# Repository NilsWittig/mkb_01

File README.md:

# mkb_01
Mechanical Keyboard 75%

https://www.instructables.com/STM32-As-HID-USB-Keyboard-STM32-Tutorials/

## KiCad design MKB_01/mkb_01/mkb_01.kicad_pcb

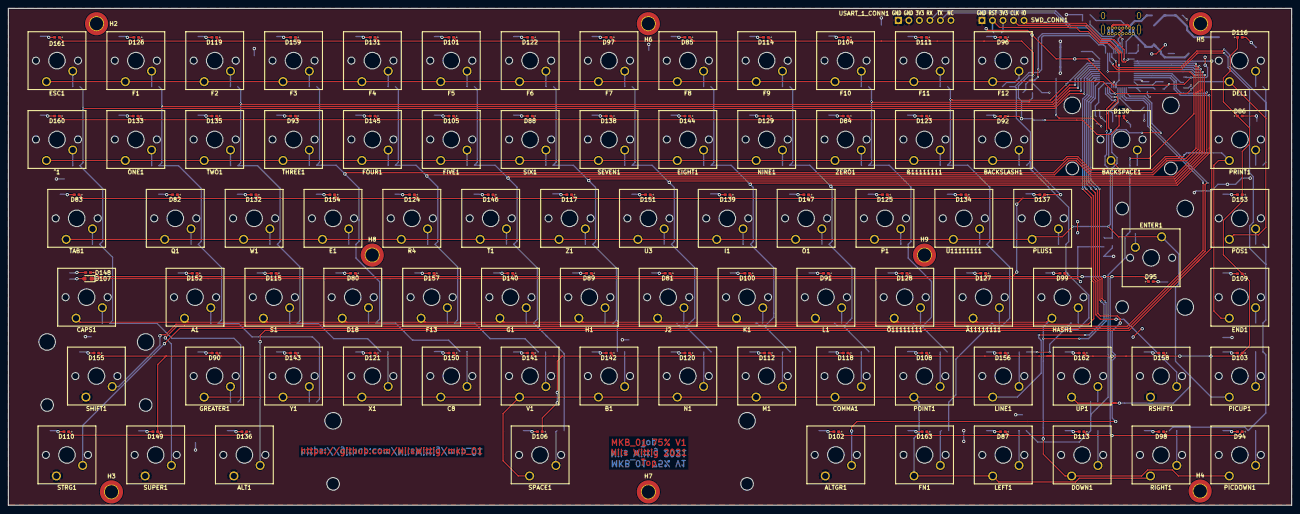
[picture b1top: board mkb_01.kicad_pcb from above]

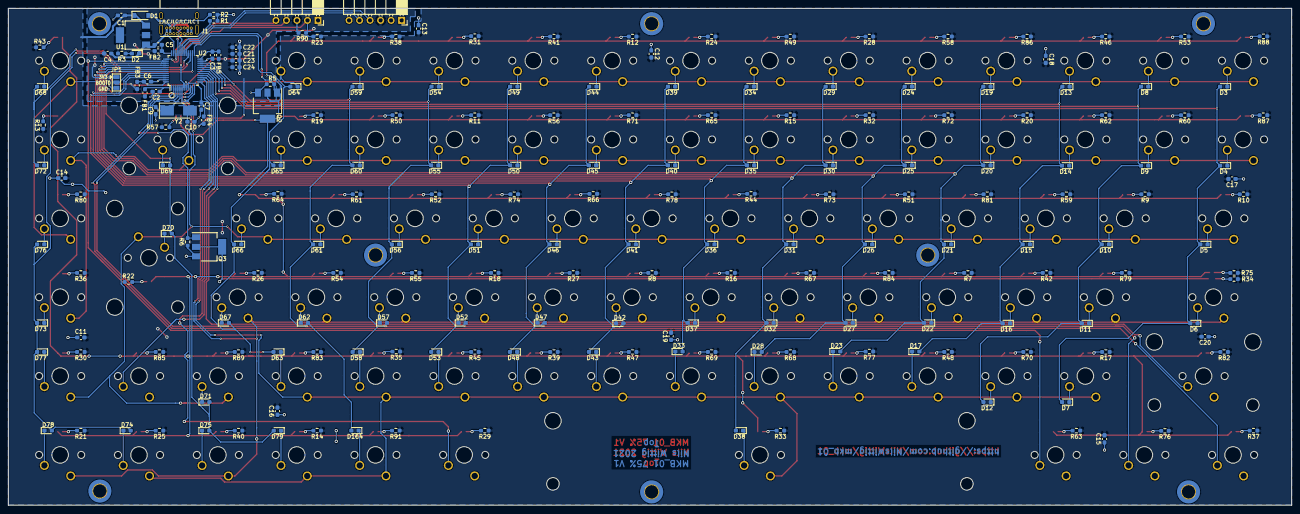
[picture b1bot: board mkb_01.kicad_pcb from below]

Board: 2 copper layers, 310.0 x 120.0 mm, 381 parts (206 on the bottom side), 214 nets.

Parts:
A1: SW_Push; SW_Cherry_MX_1.00u_PCB
ALT1: SW_Push; SW_Cherry_MX_1.25u_PCB
ALTGR1: SW_Push; SW_Cherry_MX_1.25u_PCB
B1: SW_Push; SW_Cherry_MX_1.00u_PCB
BACKSLASH1: SW_Push; SW_Cherry_MX_1.00u_PCB
BACKSPACE1: SW_Push; SW_Cherry_MX_2.00u_PCB
C1, C2, C3, C5, C6, C7: 100n; C_0603_1608Metric_Pad1.08x0.95mm_HandSolder
C4, C11, C12, C13, C14, C15, C16, C17, C18, C19, C20, C21, C22, C23, C24: 10u; C_0603_1608Metric_Pad1.08x0.95mm_HandSolder
C8: SW_Push; SW_Cherry_MX_1.00u_PCB
C9, C10: 18p; C_0603_1608Metric_Pad1.08x0.95mm_HandSolder
CAPS1: SW_Push; SW_Cherry_MX_1.75u_PCB
COMMA1: SW_Push; SW_Cherry_MX_1.00u_PCB
D1: MBR0520; D_SOD-123
D2, D107: LED red; LED_0603_1608Metric_Pad1.05x0.95mm_HandSolder
D3, D4, D5, D6, D7, D8, D9, D10, D11, D12, D13, D14, D15, D16, D17, D19, D20, D21, D22, D23, D24, D25, D26, D27, D28, D29, D30, D31, D32, D33, D34, D35, D36, D37, D38, D39, D40, D41, D42, D43, D44, D45, D46, D47, D48, D49, D50, D51, D52, D53, D54, D55, D56, D57, D58, D59, D60, D61, D62, D63, D64, D65, D66, D67, D68, D69, D70, D71, D72, D73, D74, D75, D76, D77, D78, D79, D164: 1N4148; D_0603_1608Metric_Pad1.05x0.95mm_HandSolder
D18: SW_Push; SW_Cherry_MX_1.00u_PCB
D80, D81, D82, D83, D84, D85, D86, D87, D88, D89, D90, D91, D92, D93, D94, D95, D96, D97, D98, D99, D100, D101, D102, D103, D104, D105, D106, D108, D109, D110, D111, D112, D113, D114, D115, D116, D117, D118, D119, D120, D121, D122, D123, D124, D125, D126, D127, D128, D129, D130, D131, D132, D133, D134, D135, D136, D137, D138, D139, D140, D141, D142, D143, D144, D145, D146, D147, D148, D149, D150, D151, D152, D153, D154, D155, D156, D157, D158, D159, D160, D161, D162, D163: LED amber; LED_0402_1005Metric_Pad0.77x0.64mm_HandSolder
DEL1: SW_Push; SW_Cherry_MX_1.00u_PCB
DOWN1: SW_Push; SW_Cherry_MX_1.00u_PCB
E1: SW_Push; SW_Cherry_MX_1.00u_PCB
EIGHT1: SW_Push; SW_Cherry_MX_1.00u_PCB
END1: SW_Push; SW_Cherry_MX_1.00u_PCB
ENTER1: SW_Push; SW_Cherry_MX_ISOEnter_PCB
ESC1: SW_Push; SW_Cherry_MX_1.00u_PCB
F1, F2, F3, F4, F5, F6, F7, F8, F9, F10, F11, F12, F13: SW_Push; SW_Cherry_MX_1.00u_PCB
FB1, FB2, FB3, FB4, FB5: Ferrite_Bead_Small; L_0603_1608Metric_Pad1.05x0.95mm_HandSolder
FIVE1: SW_Push; SW_Cherry_MX_1.00u_PCB
FN1: SW_Push; SW_Cherry_MX_1.00u_PCB
FOUR1: SW_Push; SW_Cherry_MX_1.00u_PCB
G1: SW_Push; SW_Cherry_MX_1.00u_PCB
GREATER1: SW_Push; SW_Cherry_MX_1.00u_PCB
H1: SW_Push; SW_Cherry_MX_1.00u_PCB
H2, H3, H4, H5, H6, H7, H8, H9: MountingHole; MountingHole_3.2mm_M3_DIN965_Pad_TopBottom
HASH1: SW_Push; SW_Cherry_MX_1.00u_PCB
I1: SW_Push; SW_Cherry_MX_1.00u_PCB
J1: USB_C_Receptacle_USB2.0; USB_C_Receptacle_GCT_USB4085
J2: SW_Push; SW_Cherry_MX_1.00u_PCB
JP1: SolderJumper_3_Open; SolderJumper-3_P1.3mm_Open_Pad1.0x1.5mm
K1: SW_Push; SW_Cherry_MX_1.00u_PCB
L1: SW_Push; SW_Cherry_MX_1.00u_PCB
LEFT1: SW_Push; SW_Cherry_MX_1.00u_PCB
LINE1: SW_Push; SW_Cherry_MX_1.00u_PCB
M1: SW_Push; SW_Cherry_MX_1.00u_PCB
N1: SW_Push; SW_Cherry_MX_1.00u_PCB
NINE1: SW_Push; SW_Cherry_MX_1.00u_PCB
O1: SW_Push; SW_Cherry_MX_1.00u_PCB
ONE1: SW_Push; SW_Cherry_MX_1.00u_PCB
P1: SW_Push; SW_Cherry_MX_1.00u_PCB
PICDOWN1: SW_Push; SW_Cherry_MX_1.00u_PCB
PICUP1: SW_Push; SW_Cherry_MX_1.00u_PCB
PLUS1: SW_Push; SW_Cherry_MX_1.00u_PCB
POINT1: SW_Push; SW_Cherry_MX_1.00u_PCB
POS1: SW_Push; SW_Cherry_MX_1.00u_PCB
PRINT1: SW_Push; SW_Cherry_MX_1.00u_PCB
Q1: SW_Push; SW_Cherry_MX_1.00u_PCB
Q2, Q3: BSP318; SOT-223-3_TabPin2
R1, R2, R5, R6, R90: 10k; R_0603_1608Metric_Pad0.98x0.95mm_HandSolder
R3, R7, R8, R9, R10, R11, R12, R13, R14, R15, R16, R17, R18, R19, R20, R21, R22, R23, R24, R25, R26, R27, R28, R29, R30, R31, R32, R33, R34, R35, R36, R37, R38, R39, R40, R41, R42, R43, R44, R45, R46, R47, R48, R49, R50, R51, R52, R53, R54, R55, R56, R57, R58, R59, R60, R61, R62, R63, R64, R65, R66, R67, R68, R69, R70, R71, R72, R73, R74, R75, R76, R77, R78, R79, R80, R81, R82, R83, R84, R85, R86, R87, R88, R89, R91: 220; R_0603_1608Metric_Pad0.98x0.95mm_HandSolder
R4: SW_Push; SW_Cherry_MX_1.00u_PCB
RIGHT1: SW_Push; SW_Cherry_MX_1.00u_PCB
RSHIFT1: SW_Push; SW_Cherry_MX_1.00u_PCB
S1: SW_Push; SW_Cherry_MX_1.00u_PCB
SEVEN1: SW_Push; SW_Cherry_MX_1.00u_PCB
SHIFT1: SW_Push; SW_Cherry_MX_2.00u_PCB
SIX1: SW_Push; SW_Cherry_MX_1.00u_PCB
SPACE1: SW_Push; SW_Cherry_MX_6.25u_PCB
STRG1: SW_Push; SW_Cherry_MX_1.25u_PCB
SUPER1: SW_Push; SW_Cherry_MX_1.00u_PCB
SWD_CONN1: Conn_01x05; PinSocket_1x05_P2.54mm_Horizontal
T1: SW_Push; SW_Cherry_MX_1.00u_PCB
TAB1: SW_Push; SW_Cherry_MX_1.50u_PCB
THREE1: SW_Push; SW_Cherry_MX_1.00u_PCB
TWO1: SW_Push; SW_Cherry_MX_1.00u_PCB
U1: LD1117S33TR_SOT223; SOT-223-3_TabPin2
U2: STM32F070CBTx; LQFP-48_7x7mm_P0.5mm
U3: SW_Push; SW_Cherry_MX_1.00u_PCB
UP1: SW_Push; SW_Cherry_MX_1.00u_PCB
USART_1_CONN1: Conn_01x06; PinSocket_1x06_P2.54mm_Horizontal
V1: SW_Push; SW_Cherry_MX_1.00u_PCB
W1: SW_Push; SW_Cherry_MX_1.00u_PCB
X1: SW_Push; SW_Cherry_MX_1.00u_PCB
Y1: SW_Push; SW_Cherry_MX_1.00u_PCB
Y2: Crystal; Crystal_SMD_Abracon_ABM3-2Pin_5.0x3.2mm_HandSoldering
Z1: SW_Push; SW_Cherry_MX_1.00u_PCB
ZERO1: SW_Push; SW_Cherry_MX_1.00u_PCB
^1: SW_Push; SW_Cherry_MX_1.00u_PCB
Ä11111111: SW_Push; SW_Cherry_MX_1.00u_PCB
Ö11111111: SW_Push; SW_Cherry_MX_1.00u_PCB
Ü11111111: SW_Push; SW_Cherry_MX_1.00u_PCB
ß11111111: SW_Push; SW_Cherry_MX_1.00u_PCB

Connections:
3V3: C4.1, C21.2, C22.2, C23.2, C24.2, FB1.1, FB2.1, FB3.1, FB4.1, FB5.1, JP1.1, R3.1, R90.2, SWD_CONN1.3, U1.2, USART_1_CONN1.3
5V: C1.1, C11.2, C12.2, C13.2, C14.2, C15.2, C16.2, C17.2, C18.2, C19.2, C20.2, D1.1, R7.1, R8.1, R9.1, R10.1, R11.1, R12.1, R13.1, R14.1, R15.1, R16.1, R17.1, R18.1, R19.1, R20.1, R21.1, R22.1, R23.1, R24.1, R25.1, R26.1, R27.1, R28.1, R29.1, R30.1, R31.1, R32.1, R33.1, R34.1, R35.1, R36.1, R37.1, R38.1, R39.1, R40.1, R41.1, R42.1, R43.1, R44.1, R45.1, R46.1, R47.1, R48.1, R49.1, R50.1, R51.1, R52.1, R53.1, R54.1, R55.1, R56.1, R57.1, R58.1, R59.1, R60.1, R61.1, R62.1, R63.1, R64.1, R65.1, R66.1, R67.1, R68.1, R69.1, R70.1, R71.1, R72.1, R73.1, R74.1, R75.1, R76.1, R77.1, R78.1, R79.1, R80.1, R81.1, R82.1, R83.1, R84.1, R85.1, R86.1, R87.1, R88.1, R89.1, R91.1, U1.3
BACK_LIGHT: Q2.1, R5.2, U2.29
CAPS_LED_GND: D107.1, Q3.2
CAPS_LIGHT: Q3.1, R6.2, U2.2
GND: ALT1.1, ALTGR1.1, C1.2, C2.2, C3.2, C4.2, C5.2, C6.2, C7.2, C9.2, C10.2, C11.1, C12.1, C13.1, C14.1, C15.1, C16.1, C17.1, C18.1, C19.1, C20.1, C21.1, C22.1, C23.1, C24.1, D2.1, J1.A1, J1.A12, J1.B1, J1.B12, J1.S1, JP1.3, Q2.3, Q3.3, R1.2, R2.1, R5.1, R6.1, RSHIFT1.1, SHIFT1.1, STRG1.1, SUPER1.1, SWD_CONN1.1, U1.1, U2.8, U2.23, U2.35, U2.47, USART_1_CONN1.1, USART_1_CONN1.2
LED_GND: D80.1, D81.1, D82.1, D83.1, D84.1, D85.1, D86.1, D87.1, D88.1, D89.1, D90.1, D91.1, D92.1, D93.1, D94.1, D95.1, D96.1, D97.1, D98.1, D99.1, D100.1, D101.1, D102.1, D103.1, D104.1, D105.1, D106.1, D108.1, D109.1, D110.1, D111.1, D112.1, D113.1, D114.1, D115.1, D116.1, D117.1, D118.1, D119.1, D120.1, D121.1, D122.1, D123.1, D124.1, D125.1, D126.1, D127.1, D128.1, D129.1, D130.1, D131.1, D132.1, D133.1, D134.1, D135.1, D136.1, D137.1, D138.1, D139.1, D140.1, D141.1, D142.1, D143.1, D144.1, D145.1, D146.1, D147.1, D148.1, D149.1, D150.1, D151.1, D152.1, D153.1, D154.1, D155.1, D156.1, D157.1, D158.1, D159.1, D160.1, D161.1, D162.1, D163.1, Q2.2
NRST: R90.1, SWD_CONN1.2, U2.7
unnamed: A1.2, D11.1
unnamed: B1.2, D33.1
unnamed: BACKSLASH1.2, D65.1
unnamed: BACKSPACE1.2, D69.1
unnamed: C2.1, FB1.2, U2.1
unnamed: C3.1, FB5.2, U2.24
unnamed: C5.1, FB2.2, U2.36
unnamed: C6.1, FB3.2, U2.48
unnamed: C7.1, FB4.2, U2.9
unnamed: C8.2, D23.1
unnamed: CAPS1.2, D6.1
unnamed: COMMA1.2, D53.1
unnamed: D1.2, J1.A4, J1.A9, J1.B4, J1.B9
unnamed: D2.2, R3.2
unnamed: D3.1, ESC1.2
unnamed: D4.1, ^1.2
unnamed: D5.1, TAB1.2
unnamed: D7.1, GREATER1.2
unnamed: D8.1, F1.2
unnamed: D9.1, ONE1.2
unnamed: D10.1, Q1.2
unnamed: D12.1, Y1.2
unnamed: D13.1, F2.2
unnamed: D14.1, TWO1.2
unnamed: D15.1, W1.2
unnamed: D16.1, S1.2
unnamed: D17.1, X1.2
unnamed: D18.2, D22.1
unnamed: D19.1, F3.2
unnamed: D20.1, THREE1.2
unnamed: D21.1, E1.2
unnamed: D24.1, F4.2
unnamed: D25.1, FOUR1.2
unnamed: D26.1, R4.2
unnamed: D27.1, F13.2
unnamed: D28.1, V1.2
unnamed: D29.1, F5.2
unnamed: D30.1, FIVE1.2
unnamed: D31.1, T1.2
unnamed: D32.1, G1.2
unnamed: D34.1, F6.2
unnamed: D35.1, SIX1.2
unnamed: D36.1, Z1.2
unnamed: D37.1, H1.2
unnamed: D38.1, SPACE1.2
unnamed: D39.1, F7.2
unnamed: D40.1, SEVEN1.2
unnamed: D41.1, U3.2
unnamed: D42.1, J2.2
unnamed: D43.1, N1.2
unnamed: D44.1, F8.2
unnamed: D45.1, EIGHT1.2
unnamed: D46.1, I1.2
unnamed: D47.1, K1.2
unnamed: D48.1, M1.2
unnamed: D49.1, F9.2
unnamed: D50.1, NINE1.2
unnamed: D51.1, O1.2
unnamed: D52.1, L1.2
unnamed: D54.1, F10.2
unnamed: D55.1, ZERO1.2
unnamed: D56.1, P1.2
unnamed: D57.1, Ö11111111.2
unnamed: D58.1, POINT1.2
unnamed: D59.1, F11.2
unnamed: D60.1, ß11111111.2
unnamed: D61.1, Ü11111111.2
unnamed: D62.1, Ä11111111.2
unnamed: D63.1, LINE1.2
unnamed: D64.1, F12.2
unnamed: D66.1, PLUS1.2
unnamed: D67.1, HASH1.2
unnamed: D68.1, DEL1.2
unnamed: D70.1, ENTER1.2
unnamed: D71.1, UP1.2
unnamed: D72.1, PRINT1.2
unnamed: D73.1, END1.2
unnamed: D74.1, RIGHT1.2
unnamed: D75.1, DOWN1.2
unnamed: D76.1, POS1.2
unnamed: D77.1, PICUP1.2
unnamed: D78.1, PICDOWN1.2
unnamed: D79.1, LEFT1.2
unnamed: D80.2, R7.2
unnamed: D81.2, R8.2
unnamed: D82.2, R9.2
unnamed: D83.2, R10.2
unnamed: D84.2, R11.2
unnamed: D85.2, R12.2
unnamed: D86.2, R13.2
unnamed: D87.2, R14.2
unnamed: D88.2, R15.2
unnamed: D89.2, R16.2
unnamed: D90.2, R17.2
unnamed: D91.2, R18.2
unnamed: D92.2, R19.2
unnamed: D93.2, R20.2
unnamed: D94.2, R21.2
unnamed: D95.2, R22.2
unnamed: D96.2, R23.2
unnamed: D97.2, R24.2
unnamed: D98.2, R25.2
unnamed: D99.2, R26.2
unnamed: D100.2, R27.2
unnamed: D101.2, R28.2
unnamed: D102.2, R29.2
unnamed: D103.2, R30.2
unnamed: D104.2, R31.2
unnamed: D105.2, R32.2
unnamed: D106.2, R33.2
unnamed: D107.2, R34.2
unnamed: D108.2, R35.2
unnamed: D109.2, R36.2
unnamed: D110.2, R37.2
unnamed: D111.2, R38.2
unnamed: D112.2, R39.2
unnamed: D113.2, R40.2
unnamed: D114.2, R41.2
unnamed: D115.2, R42.2
unnamed: D116.2, R43.2
unnamed: D117.2, R44.2
unnamed: D118.2, R45.2
unnamed: D119.2, R46.2
unnamed: D120.2, R47.2
unnamed: D121.2, R48.2
unnamed: D122.2, R49.2
unnamed: D123.2, R50.2
unnamed: D124.2, R51.2
unnamed: D125.2, R52.2
unnamed: D126.2, R53.2
unnamed: D127.2, R54.2
unnamed: D128.2, R55.2
unnamed: D129.2, R56.2
unnamed: D130.2, R57.2
unnamed: D131.2, R58.2
unnamed: D132.2, R59.2
unnamed: D133.2, R60.2
unnamed: D134.2, R61.2
unnamed: D135.2, R62.2
unnamed: D136.2, R63.2
unnamed: D137.2, R64.2
unnamed: D138.2, R65.2
unnamed: D139.2, R66.2
unnamed: D140.2, R67.2
unnamed: D141.2, R68.2
unnamed: D142.2, R69.2
unnamed: D143.2, R70.2
unnamed: D144.2, R71.2
unnamed: D145.2, R72.2
unnamed: D146.2, R73.2
unnamed: D147.2, R74.2
unnamed: D148.2, R75.2
unnamed: D149.2, R76.2
unnamed: D150.2, R77.2
unnamed: D151.2, R78.2
unnamed: D152.2, R79.2
unnamed: D153.2, R80.2
unnamed: D154.2, R81.2
unnamed: D155.2, R82.2
unnamed: D156.2, R83.2
unnamed: D157.2, R84.2
unnamed: D158.2, R85.2
unnamed: D159.2, R86.2
unnamed: D160.2, R87.2
unnamed: D161.2, R88.2
unnamed: D162.2, R89.2
unnamed: D163.2, R91.2
unnamed: D164.1, FN1.2
unnamed: J1.A5, R1.1
unnamed: J1.B5, R2.2
unnamed: JP1.2, U2.44
OSC_IN: C9.1, U2.5, Y2.1
OSC_OUT: C10.1, U2.6, Y2.2
PA0: DEL1.1, ESC1.1, F1.1, F2.1, F3.1, F4.1, F5.1, F6.1, F7.1, F8.1, F9.1, F10.1, F11.1, F12.1, POS1.1, U2.10
PA1: BACKSLASH1.1, BACKSPACE1.1, EIGHT1.1, END1.1, FIVE1.1, FOUR1.1, NINE1.1, ONE1.1, PRINT1.1, SEVEN1.1, SIX1.1, THREE1.1, TWO1.1, U2.11, ZERO1.1, ^1.1, ß11111111.1
PA2: E1.1, ENTER1.1, I1.1, O1.1, P1.1, PICUP1.1, PLUS1.1, Q1.1, R4.1, T1.1, TAB1.1, U2.12, U3.1, UP1.1, W1.1, Z1.1, Ü11111111.1
PA3: A1.1, CAPS1.1, D18.1, DOWN1.1, F13.1, G1.1, H1.1, HASH1.1, J2.1, K1.1, L1.1, PICDOWN1.1, S1.1, U2.13, Ä11111111.1, Ö11111111.1
PA4: B1.1, C8.1, COMMA1.1, FN1.1, GREATER1.1, LEFT1.1, LINE1.1, M1.1, N1.1, POINT1.1, RIGHT1.1, SPACE1.1, U2.14, V1.1, X1.1, Y1.1
PA5: ALTGR1.2, U2.15
PA6: RSHIFT1.2, U2.16
PA7: SHIFT1.2, U2.17
PA15: ALT1.2, U2.38
PB0: D3.2, D4.2, D5.2, D6.2, D7.2, U2.18
PB1: D8.2, D9.2, D10.2, D11.2, D12.2, U2.19
PB2: D13.2, D14.2, D15.2, D16.2, D17.2, U2.20
PB3: D19.2, D20.2, D21.2, D22.2, D23.2, U2.39
PB4: D24.2, D25.2, D26.2, D27.2, D28.2, U2.40
PB5: D29.2, D30.2, D31.2, D32.2, D38.2, U2.41
PB6: D33.2, D34.2, D35.2, D36.2, D37.2, U2.42
PB7: D39.2, D40.2, D41.2, D42.2, D43.2, U2.43
PB8: D44.2, D45.2, D46.2, D47.2, D48.2, U2.45
PB9: D49.2, D50.2, D51.2, D52.2, D53.2, U2.46
PB10: D54.2, D55.2, D56.2, D57.2, D58.2, U2.21
PB11: D59.2, D60.2, D61.2, D62.2, D164.2, U2.22
PB12: D63.2, D64.2, D65.2, D66.2, D67.2, U2.25
PB13: D69.2, D70.2, D71.2, D75.2, D79.2, U2.26
PB14: D73.2, D74.2, D76.2, D77.2, D78.2, U2.27
PB15: D68.2, D72.2, U2.28
PC14: STRG1.2, U2.3
PC15: SUPER1.2, U2.4
SWDCLK: SWD_CONN1.4, U2.37
SWDIO: SWD_CONN1.5, U2.34
USART_1_RX: U2.31, USART_1_CONN1.4
USART_1_TX: U2.30, USART_1_CONN1.5
USB_DM: J1.A7, J1.B7, U2.32
USB_DP: J1.A6, J1.B6, U2.33

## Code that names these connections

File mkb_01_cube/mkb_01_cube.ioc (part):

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Mcu.Name=STM32F070CBTx
Mcu.Package=LQFP48
Mcu.UserName=STM32F070CBTx
PA0.GPIOParameters=GPIO_Label
PA0.GPIO_Label=Row_0
PA0.Signal=GPIO_Input
PA1.GPIOParameters=GPIO_Label
PA1.GPIO_Label=Row_1
PA1.Signal=GPIO_Input
PA10.Mode=Asynchronous
PA10.Signal=USART1_RX
PA11.Mode=Device
PA11.Signal=USB_DM
PA12.Mode=Device
PA12.Signal=USB_DP
PA13.Mode=Serial_Wire
PA13.Signal=SYS_SWDIO
PA14.Mode=Serial_Wire
PA14.Signal=SYS_SWCLK
PA15.GPIOParameters=GPIO_Label
PA15.GPIO_Label=ALT
PA15.Signal=GPIO_Input
PA2.GPIOParameters=GPIO_Label
PA2.GPIO_Label=Row_2
PA2.Signal=GPIO_Input
PA3.GPIOParameters=GPIO_Label
PA3.GPIO_Label=Row_3
PA3.Signal=GPIO_Input
PA4.GPIOParameters=GPIO_Label
PA4.GPIO_Label=Row_4
PA4.Signal=GPIO_Input
PA5.GPIOParameters=GPIO_Label
PA5.GPIO_Label=ALTGR
PA5.Signal=GPIO_Input
PA6.GPIOParameters=GPIO_Label
PA6.GPIO_Label=LSHIFT
PA6.Signal=GPIO_Input
PA7.GPIOParameters=GPIO_Label
PA7.GPIO_Label=SHIFT
PA7.Signal=GPIO_Input
PA8.GPIOParameters=GPIO_Label
PA8.GPIO_Label=BACK_LIGHT
PA8.Signal=S_TIM1_CH1
PA9.Mode=Asynchronous
PA9.Signal=USART1_TX
PB0.GPIOParameters=GPIO_Label
PB0.GPIO_Label=COL_0
PB0.Signal=GPIO_Input
PB1.GPIOParameters=GPIO_Label
PB1.GPIO_Label=COL_1
PB1.Signal=GPIO_Input
PB10.GPIOParameters=GPIO_Label
PB10.GPIO_Label=COL_10
PB10.Signal=GPIO_Input
PB11.GPIOParameters=GPIO_Label
PB11.GPIO_Label=COL_11
PB11.Signal=GPIO_Input
PB12.GPIOParameters=GPIO_Label
PB12.GPIO_Label=COL_12
PB12.Signal=GPIO_Input
PB13.GPIOParameters=GPIO_Label
PB13.GPIO_Label=COL_13
PB13.Signal=GPIO_Input
PB14.GPIOParameters=GPIO_Label
PB14.GPIO_Label=COL_14
PB14.Signal=GPIO_Input
PB15.GPIOParameters=GPIO_Label
PB15.GPIO_Label=COL_15
PB15.Signal=GPIO_Input
PB2.GPIOParameters=GPIO_Label
PB2.GPIO_Label=COL_2
PB2.Signal=GPIO_Input
PB3.GPIOParameters=GPIO_Label
PB3.GPIO_Label=COL_3
PB3.Signal=GPIO_Input
PB4.GPIOParameters=GPIO_Label
PB4.GPIO_Label=COL_4
PB4.Signal=GPIO_Input
PB5.GPIOParameters=GPIO_Label
PB5.GPIO_Label=COL_5
PB5.Signal=GPIO_Input
PB6.GPIOParameters=GPIO_Label
PB6.GPIO_Label=COL_6
PB6.Signal=GPIO_Input
PB7.GPIOParameters=GPIO_Label
PB7.GPIO_Label=COL_7
PB7.Signal=GPIO_Input
PB8.GPIOParameters=GPIO_Label
PB8.GPIO_Label=COL_8
PB8.Signal=GPIO_Input
PB9.GPIOParameters=GPIO_Label
PB9.GPIO_Label=COL_9
PB9.Signal=GPIO_Input
PC13.GPIOParameters=GPIO_Label
PC13.GPIO_Label=CAPS_LIGHT
PC13.Signal=GPIO_Output
PC14-OSC32_IN.GPIOParameters=GPIO_Label
PC14-OSC32_IN.GPIO_Label=CTL
PC14-OSC32_IN.Signal=GPIO_Input
PC15-OSC32_OUT.GPIOParameters=GPIO_Label
PC15-OSC32_OUT.GPIO_Label=SUPER
PC15-OSC32_OUT.Signal=GPIO_Input
PF0-OSC_IN.Mode=HSE-External-Oscillator
PF0-OSC_IN.Signal=RCC_OSC_IN
PF1-OSC_OUT.Mode=HSE-External-Oscillator
PF1-OSC_OUT.Signal=RCC_OSC_OUT
RCC.SYSCLKFreq_VALUE=48000000
RCC.SYSCLKSource=RCC_SYSCLKSOURCE_PLLCLK
board=custom

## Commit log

2021-03-11 put project in repo
2021-03-11 added FN key fixed layout
2021-03-12 changed quartz, finished placing and layers, some routing done
2021-03-13 routing somewhat finished
2021-03-14 fixed silkscreen markings, exported and checked jlcpcb
2021-03-15 added ferrit beads and optimized pcb a bit
2021-03-16 change diode direction to read from column rather than rows, added some more caps for the mcu, updated BOM
2021-03-16 routing optimizations
2021-03-17 add layout image
2021-03-19 ordered
2021-03-27 parts arrived added orders
2021-03-28 started designing case
2021-03-30 soldered and tested mcu
2021-06-25 resoldered and started new fw
2021-06-25 keyboard now recognised by pc
2021-06-25 try change product string
2021-06-25 device name changed, problems with pullups
2023-01-24 some schematic rework
